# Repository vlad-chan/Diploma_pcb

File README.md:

# Diploma_pcb
Repository for my diploma work. PCB design and schematic.

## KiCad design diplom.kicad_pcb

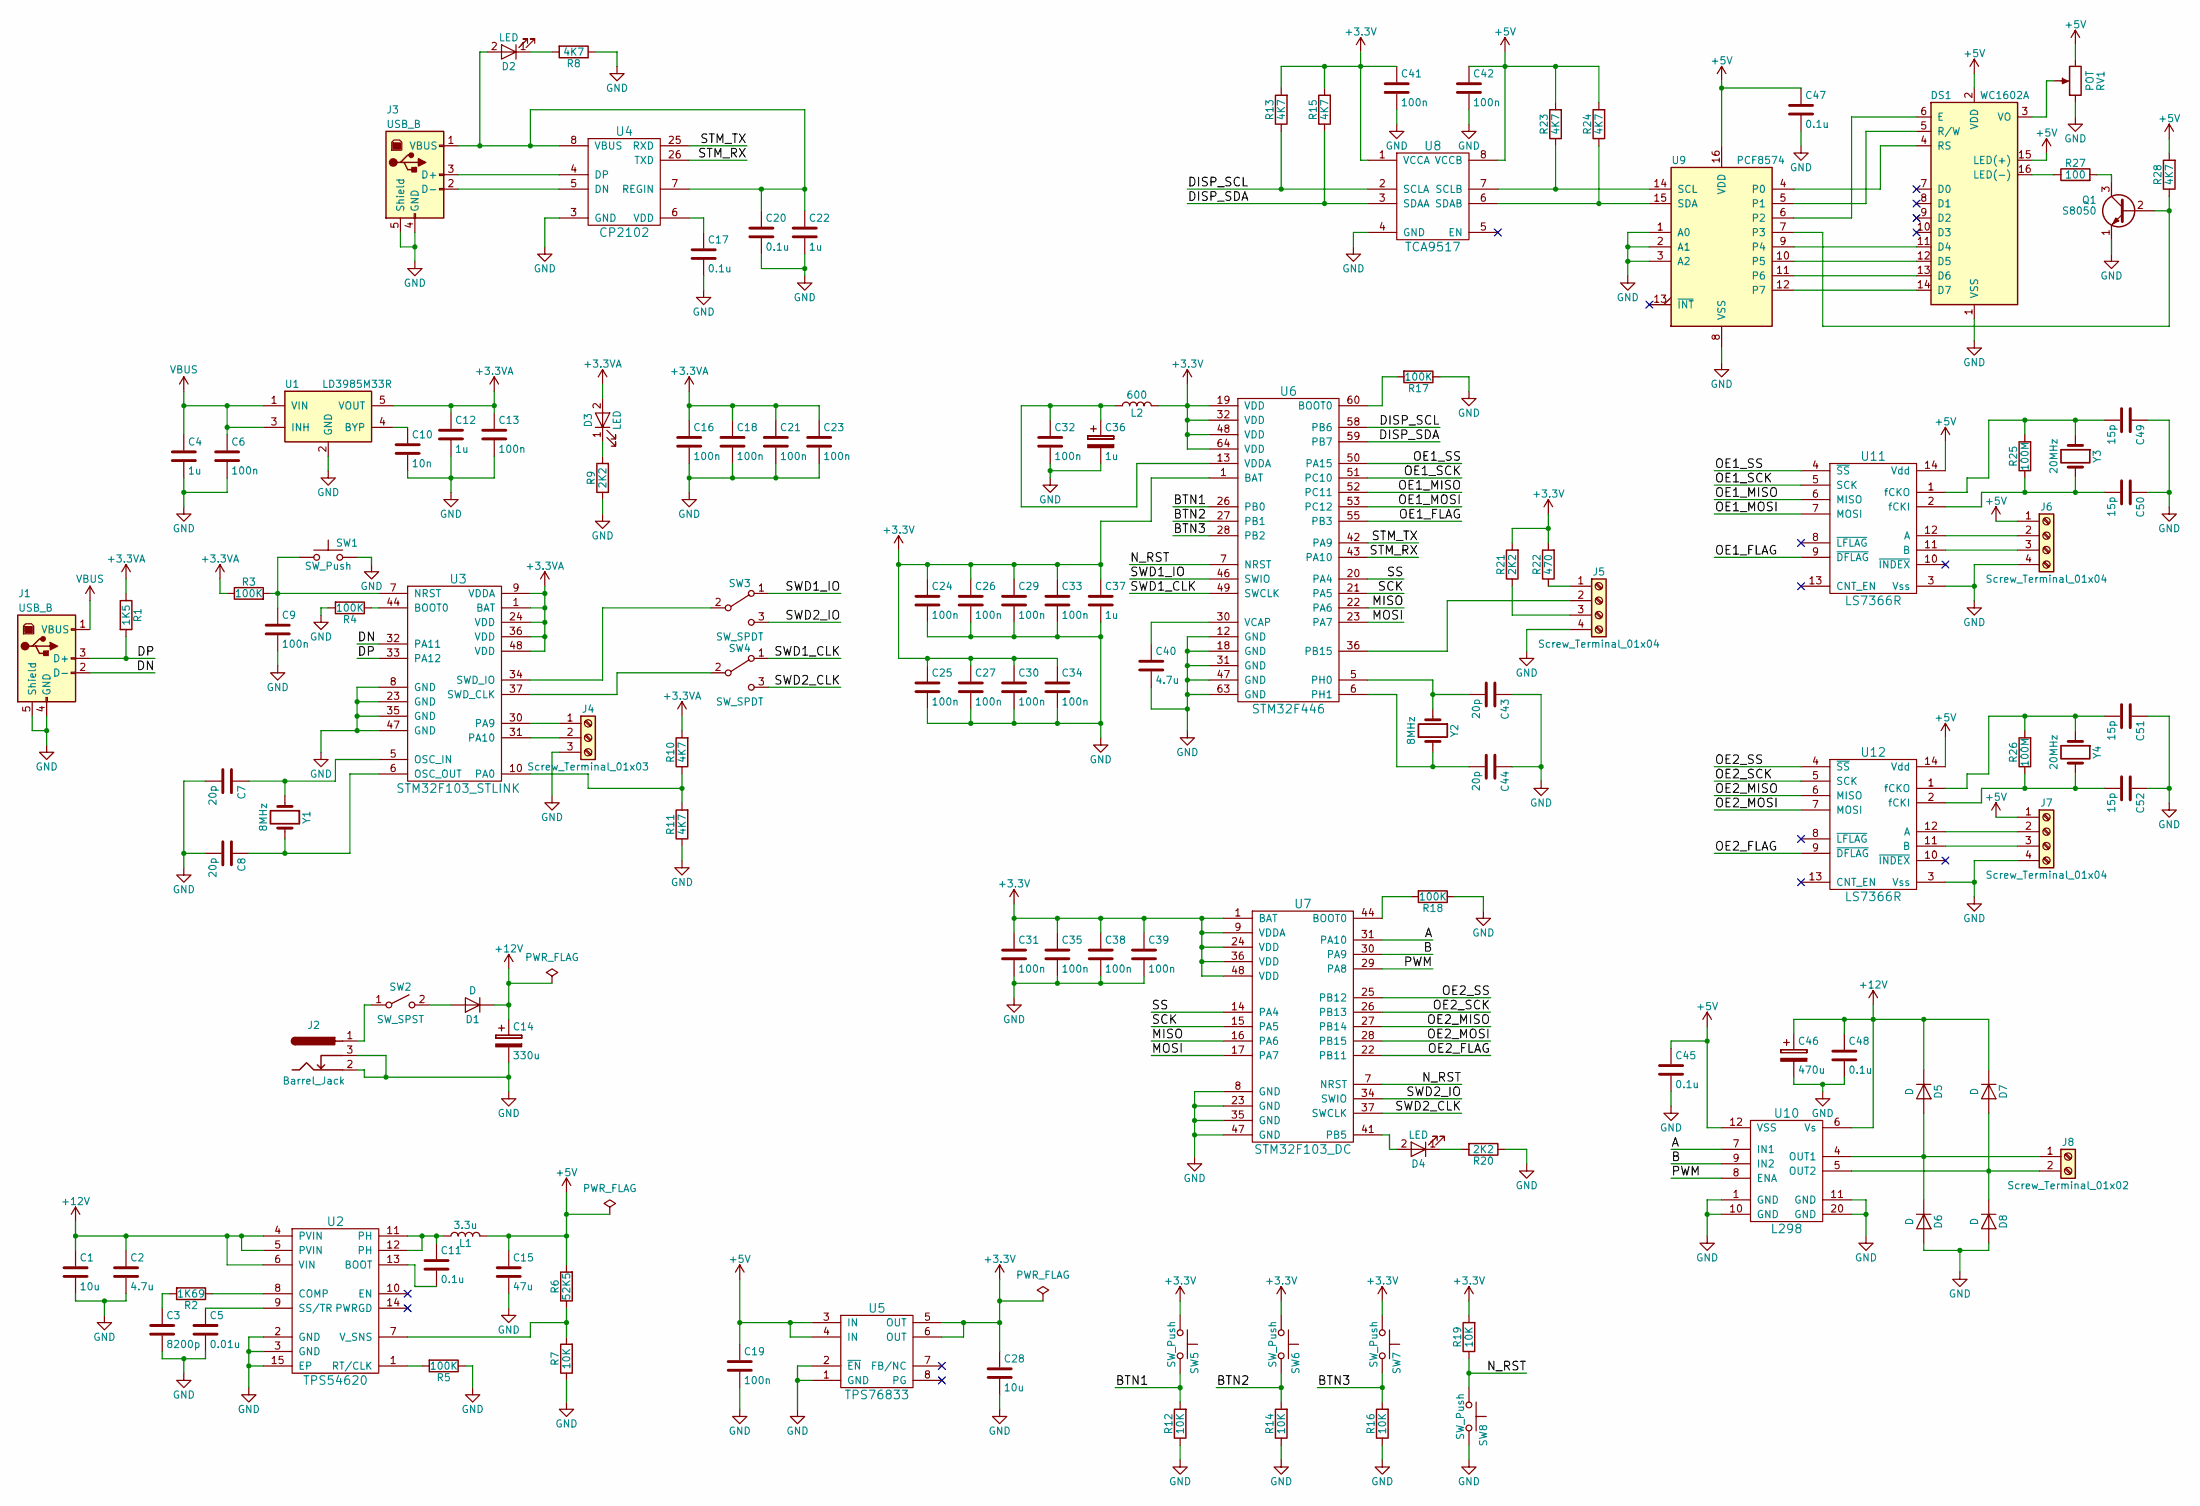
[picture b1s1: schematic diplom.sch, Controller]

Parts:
C1, C28: 10u; C_1206_HandSoldering
C2, C40: 4.7u; C_0805_HandSoldering
C3: 8200p; C_0603_HandSoldering
C4, C12, C22, C37: 1u; C_0805_HandSoldering
C5: 0.01u; C_0603_HandSoldering
C6, C9, C13, C16, C18, C19, C21, C23, C24, C25, C26, C27, C29, C30, C31, C32, C33, C34, C35, C38, C39, C41, C42: 100n; C_0603_HandSoldering
C7, C8, C43, C44: 20p; C_0603_HandSoldering
C10: 10n; C_0603_HandSoldering
C11, C17, C20, C45, C47: 0.1u; C_0603_HandSoldering
C14: 330u; CP_Elec_10x10
C15: 47u; C_1206_HandSoldering
C36: 1u; C_1210_HandSoldering
C46: 470u; CP_Elec_10x10
C48: 0.1u; C_0805_HandSoldering
C49, C50, C51, C52: 15p; C_0603_HandSoldering
D1, D5, D6, D7, D8: D; D_SMA_Handsoldering
D2, D3, D4: LED; D_0805
DS1: WC1602A
J1, J3: USB_B; USB_Micro-B_Molex_47346-0001
J2: Barrel_Jack; BARREL_JACK
J4: Screw_Terminal_01x03; Pin_Header_Straight_1x03_Pitch2.54mm
J5, J6, J7: Screw_Terminal_01x04; Pin_Header_Straight_1x04_Pitch2.54mm
J8: Screw_Terminal_01x02; Pin_Header_Straight_1x02_Pitch2.54mm
L1: 3.3u; L_10.4x10.4_H4.8
L2: 600; L_0603_HandSoldering
Q1: S8050; TO-92_Molded_Narrow
R1: 1K5; R_0603_HandSoldering
R2: 1K69; R_0603_HandSoldering
R3, R4, R5, R17, R18: 100K; R_0603_HandSoldering
R6: 52K5; R_0603_HandSoldering
R7, R12, R14, R16, R19: 10K; R_0603_HandSoldering
R8, R10, R11, R13, R15, R23, R24, R28: 4K7; R_0603_HandSoldering
R9, R20, R21: 2K2; R_0603_HandSoldering
R22: 470; R_0603_HandSoldering
R25, R26: 100M; R_0603_HandSoldering
R27: 100; R_1210_HandSoldering
RV1: POT; Potentiometer_Trimmer_ACP_CA14VSMD_Horizontal_Px13.0mm_Py10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
SW1, SW5, SW6, SW7, SW8: SW_Push; SW_SPST_B3U-1000P
SW2: SW_SPST; Pin_Header_Straight_1x03_Pitch2.54mm
SW3, SW4: SW_SPDT; Pin_Header_Straight_1x03_Pitch2.54mm
U1: LD3985M33R; SOT-23-5_HandSoldering
U2: TPS54620; TPS54620_PVQFN-N14
U3: STM32F103_STLINK; LQFP-48_7x7mm_Pitch0.5mm
U4: CP2102; QFN-28-1EP_4x4mm_Pitch0.4mm
U5: TPS76833; SOIC-8-N
U6: STM32F446; LQFP-64_10x10mm_Pitch0.5mm
U7: STM32F103_DC; LQFP-48_7x7mm_Pitch0.5mm
U8: TCA9517; SOIC-8-N
U9: PCF8574; SO-16-L
U10: L298; HSOP-20-1EP_11.0x15.9mm_Pitch1.27mm_SlugDown_ThermalVias
U11, U12: LS7366R; SOIC-14_3.9x8.7mm_Pitch1.27mm
Y1, Y2: 8MHz; Crystal_SMD_EuroQuartz_MQ2-2pin_7.0x5.0mm_HandSoldering
Y3, Y4: 20MHz; Crystal_SMD_EuroQuartz_MQ2-2pin_7.0x5.0mm_HandSoldering

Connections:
+3.3VA: C12.1, C13.1, C16.1, C18.1, C21.1, C23.1, D3.2 (A), R1.1, R3.1, R10.2, U1.5 (VOUT), U3.1 (BAT), U3.9 (VDDA), U3.24 (VDD), U3.36 (VDD), U3.48 (VDD)
+3V3: C24.1, C25.1, C26.1, C27.1, C28.1, C29.1, C30.1, C31.1, C33.1, C34.1, C35.1, C37.1, C38.1, C39.1, C41.1, L2.2, R13.2, R15.2, R19.2, R21.2, R22.2, SW5.1, SW6.1, SW7.1, U5.5 (OUT), U5.6 (OUT), U6.1 (BAT), U6.19 (VDD), U6.32 (VDD), U6.48 (VDD), U6.64 (VDD), U7.1 (BAT), U7.9 (VDDA), U7.24 (VDD), U7.36 (VDD), U7.48 (VDD), U8.1 (VCCA)
+5V: C15.1, C19.1, C42.1, C45.1, C47.1, DS1.2 (VDD), DS1.15 (LED(+)), J6.1, J7.1, L1.2, R6.2, R23.2, R24.2, R28.2, RV1.3, U5.3 (IN), U5.4 (IN), U8.8 (VCCB), U9.16 (VDD), U10.12 (VSS), U11.14 (Vdd), U12.14 (Vdd)
+12V: C1.1, C2.1, C14.1, C46.1, C48.1, D1.1 (K), D5.1 (K), D7.1 (K), U2.4 (PVIN), U2.5 (PVIN), U2.6 (VIN), U10.6 (Vs)
/A: U7.31 (PA10), U10.7 (IN1)
/B: U7.30 (PA9), U10.9 (IN2)
/BTN1: R12.2, SW5.2, U6.26 (PB0)
/BTN2: R14.2, SW6.2, U6.27 (PB1)
/BTN3: R16.2, SW7.2, U6.28 (PB2)
/DISP_SCL: R13.1, U6.58 (PB6), U8.2 (SCLA)
/DISP_SDA: R15.1, U6.59 (PB7), U8.3 (SDAA)
/DN: J1.2 (D-), U3.32 (PA11)
/DP: J1.3 (D+), R1.2, U3.33 (PA12)
/MISO: U6.22 (PA6), U7.16 (PA6)
/MOSI: U6.23 (PA7), U7.17 (PA7)
/N_RST: R19.1, SW8.1, U6.7 (NRST), U7.7 (NRST)
/OE1_FLAG: U6.55 (PB3), U11.9 (~DFLAG)
/OE1_MISO: U6.52 (PC11), U11.6 (MISO)
/OE1_MOSI: U6.53 (PC12), U11.7 (MOSI)
/OE1_SCK: U6.51 (PC10), U11.5 (SCK)
/OE1_SS: U6.50 (PA15), U11.4 (~SS)
/OE2_FLAG: U7.22 (PB11), U12.9 (~DFLAG)
/OE2_MISO: U7.27 (PB14), U12.6 (MISO)
/OE2_MOSI: U7.28 (PB15), U12.7 (MOSI)
/OE2_SCK: U7.26 (PB13), U12.5 (SCK)
/OE2_SS: U7.25 (PB12), U12.4 (~SS)
/PWM: U7.29 (PA8), U10.8 (ENA)
/SCK: U6.21 (PA5), U7.15 (PA5)
/SS: U6.20 (PA4), U7.14 (PA4)
/STM_RX: U4.26 (TXD), U6.43 (PA10)
/STM_TX: U4.25 (RXD), U6.42 (PA9)
/SWD1_CLK: SW4.1 (A), U6.49 (SWCLK)
/SWD1_IO: SW3.1 (A), U6.46 (SWIO)
/SWD2_CLK: SW4.3 (C), U7.37 (SWCLK)
/SWD2_IO: SW3.3 (C), U7.34 (SWIO)
GND: C1.2, C2.2, C3.2, C4.2, C5.2, C6.2, C7.2, C8.2, C9.2, C10.2, C12.2, C13.2, C14.2, C15.2, C16.2, C17.2, C18.2, C19.2, C20.2, C21.2, C22.2, C23.2, C24.2, C25.2, C26.2, C27.2, C28.2, C29.2, C30.2, C31.2, C32.2, C33.2, C34.2, C35.2, C36.2, C37.2, C38.2, C39.2, C40.2, C41.2, C42.2, C43.1, C44.1, C45.2, C46.2, C47.2, C48.2, C49.1, C50.1, C51.1, C52.1, D6.2 (A), D8.2 (A), DS1.1 (VSS), J1.4 (GND), J1.5 (Shield), J2.2, J2.3, J3.4 (GND), J3.5 (Shield), J4.3, J5.4, J6.4, J7.4, Q1.1 (E), R4.2, R5.1, R7.1, R8.1, R9.1, R11.1, R12.1, R14.1, R16.1, R17.1, R18.1, R20.1, RV1.1, SW1.2, SW8.2, U1.2 (GND), U2.2 (GND), U2.3 (GND), U2.15 (EP), U3.8 (GND), U3.23 (GND), U3.35 (GND), U3.47 (GND), U4.3 (GND), U4.29, U5.1 (GND), U5.2 (~EN), U6.12 (GND), U6.18 (GND), U6.31 (GND), U6.47 (GND), U6.63 (GND), U7.8 (GND), U7.23 (GND), U7.35 (GND), U7.47 (GND), U8.4 (GND), U9.1 (A0), U9.2 (A1), U9.3 (A2), U9.8 (VSS), U10.1 (GND), U10.10 (GND), U10.11 (GND), U10.20 (GND), U10.21, U11.3 (Vss), U12.3 (Vss)
unnamed: C3.1, R2.2
unnamed: C5.1, U2.9 (SS/TR)
unnamed: C7.1, U3.5 (OSC_IN), Y1.1
unnamed: C8.1, U3.6 (OSC_OUT), Y1.2
unnamed: C9.1, R3.2, SW1.1, U3.7 (NRST)
unnamed: C10.1, U1.4 (BYP)
unnamed: C11.1, L1.1, U2.11 (PH), U2.12 (PH)
unnamed: C11.2, U2.13 (BOOT)
unnamed: C17.1, U4.6 (VDD)
unnamed: C20.1, C22.1, D2.2 (A), J3.1 (VBUS), U4.7 (REGIN), U4.8 (VBUS)
unnamed: C32.1, C36.1, L2.1, U6.13 (VDDA)
unnamed: C40.1, U6.30 (VCAP)
unnamed: C43.2, U6.5 (PH0), Y2.1
unnamed: C44.2, U6.6 (PH1), Y2.2
unnamed: C49.2, R25.2, U11.1 (fCKO), Y3.1
unnamed: C50.2, R25.1, U11.2 (fCKI), Y3.2
unnamed: C51.2, R26.2, U12.1 (fCKO), Y4.1
unnamed: C52.2, R26.1, U12.2 (fCKI), Y4.2
unnamed: D1.2 (A), SW2.2 (B)
unnamed: D2.1 (K), R8.2
unnamed: D3.1 (K), R9.2
unnamed: D4.1 (K), R20.2
unnamed: D4.2 (A), U7.41 (PB5)
unnamed: D5.2 (A), D6.1 (K), J8.1, U10.4 (OUT1)
unnamed: D7.2 (A), D8.1 (K), J8.2, U10.5 (OUT2)
unnamed: DS1.3 (VO), RV1.2
unnamed: DS1.4 (RS), U9.4 (P0)
unnamed: DS1.5 (R/W), U9.5 (P1)
unnamed: DS1.6 (E), U9.6 (P2)
unnamed: DS1.11 (D4), U9.9 (P4)
unnamed: DS1.12 (D5), U9.10 (P5)
unnamed: DS1.13 (D6), U9.11 (P6)
unnamed: DS1.14 (D7), U9.12 (P7)
unnamed: DS1.16 (LED(-)), R27.1
unnamed: J2.1, SW2.1 (A)
unnamed: J3.2 (D-), U4.5 (DN)
unnamed: J3.3 (D+), U4.4 (DP)
unnamed: J4.1, U3.30 (PA9)
unnamed: J4.2, U3.31 (PA10)
unnamed: J5.1, R22.1
unnamed: J5.2, U6.36 (PB15)
unnamed: J5.3, R21.1
unnamed: J6.2, U11.12 (A)
unnamed: J6.3, U11.11 (B)
unnamed: J7.2, U12.12 (A)
unnamed: J7.3, U12.11 (B)
unnamed: Q1.2 (B), R28.1, U9.7 (P3)
unnamed: Q1.3 (C), R27.2
unnamed: R2.1, U2.8 (COMP)
unnamed: R4.1, U3.44 (BOOT0)
unnamed: R5.2, U2.1 (RT/CLK)
unnamed: R6.1, R7.2, U2.7 (V_SNS)
unnamed: R10.1, R11.2, U3.10 (PA0)
unnamed: R17.2, U6.60 (BOOT0)
unnamed: R18.2, U7.44 (BOOT0)
unnamed: R23.1, U8.7 (SCLB), U9.14 (SCL)
unnamed: R24.1, U8.6 (SDAB), U9.15 (SDA)
unnamed: SW3.2 (B), U3.34 (SWD_IO)
unnamed: SW4.2 (B), U3.37 (SWD_CLK)
VBUS: C4.1, C6.1, J1.1 (VBUS), U1.1 (VIN), U1.3 (INH)

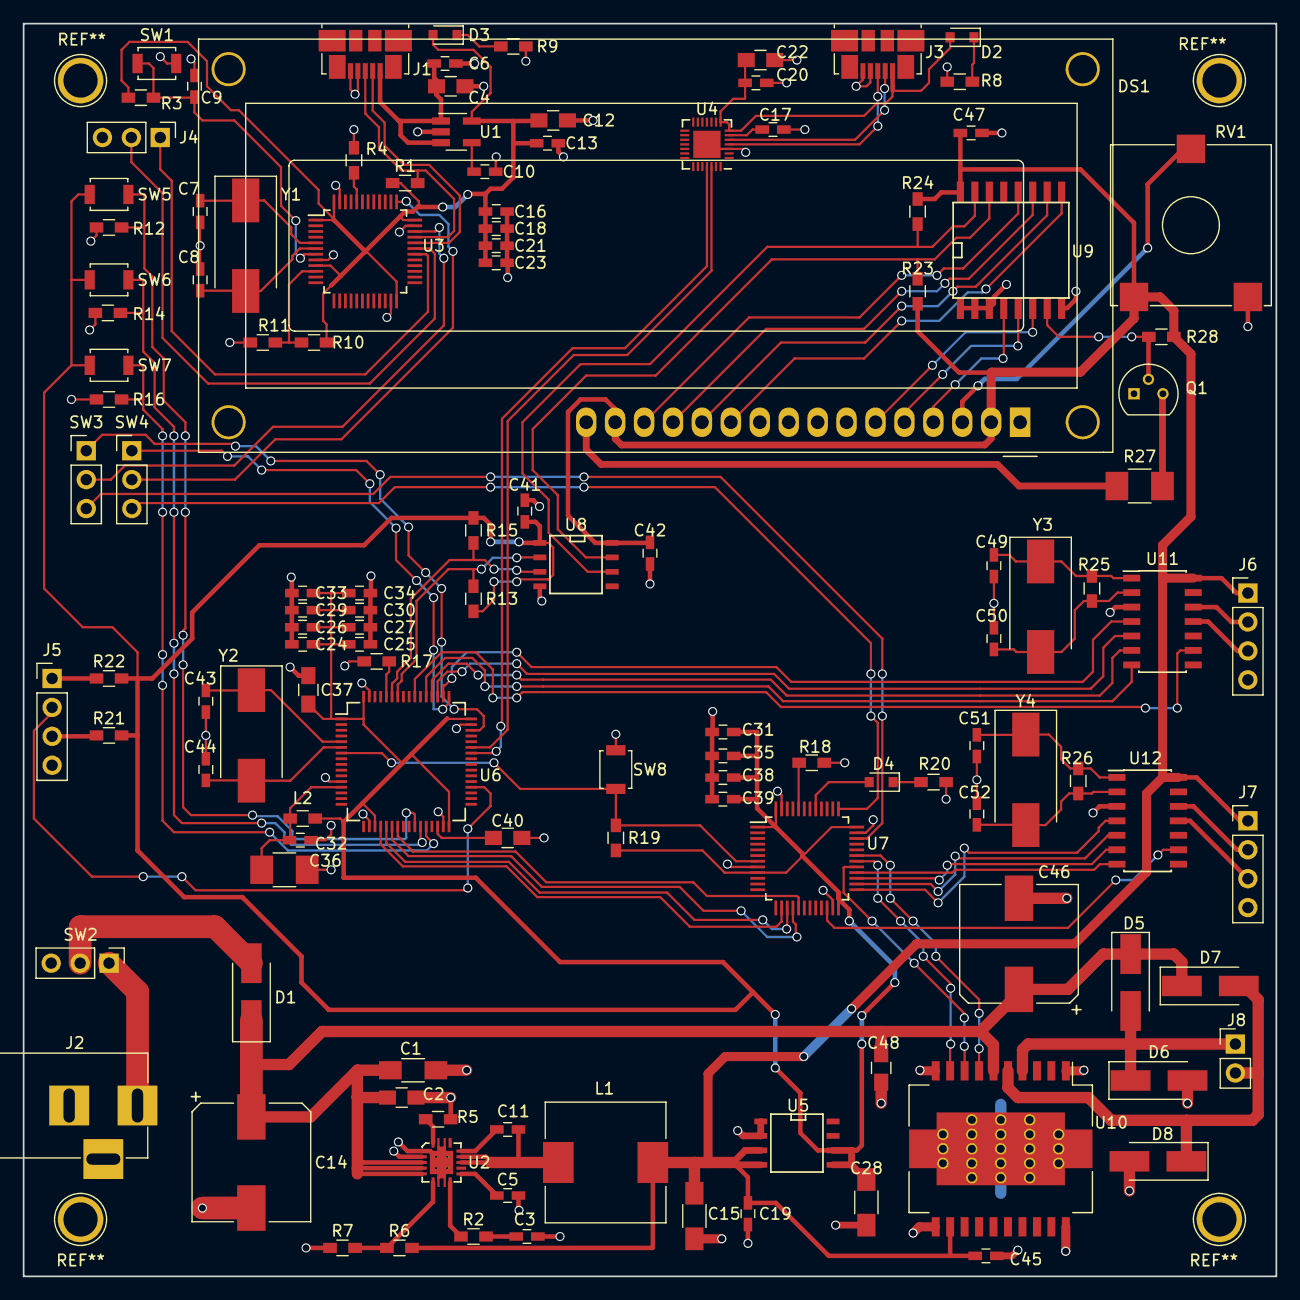
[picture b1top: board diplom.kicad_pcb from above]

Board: 2 copper layers, 110.0 x 110.0 mm, 125 parts (0 on the bottom side), 96 nets.

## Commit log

2017-11-02 Project created
2017-11-06 R,C,L,D libs added
2017-11-27 Sync from home
2017-11-27 Power added
2017-11-28 Electric schema added
2017-11-30 TPS54620 footprint added. Annotations
2017-12-03 Schematic changed
2017-12-03 Elements reannotated
2017-12-04 Footprints placed on PCB
2017-12-06 PCB routing started. Quartz footprint changed
2017-12-07 Schematic redraw. Wire redrawing for correctness
2017-12-08 PCB redrawing with correct net
2017-12-10 PCB routed
2017-12-11 Silkscreens changed
